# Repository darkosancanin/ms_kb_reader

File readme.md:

## Overview 
ATmega328 based Microsoft wireless keyboard reader with LCD display. 
The device passively scans for wireless keyboards in the vicinity of the device, then displays the characters typed on the LCD display. 
Based on code from KeySweeper (http://samy.pl/keysweeper/) by Samy Kamkar. 

## Keyboard Reader

## Schematic

## Breadboard

## PCB Layout

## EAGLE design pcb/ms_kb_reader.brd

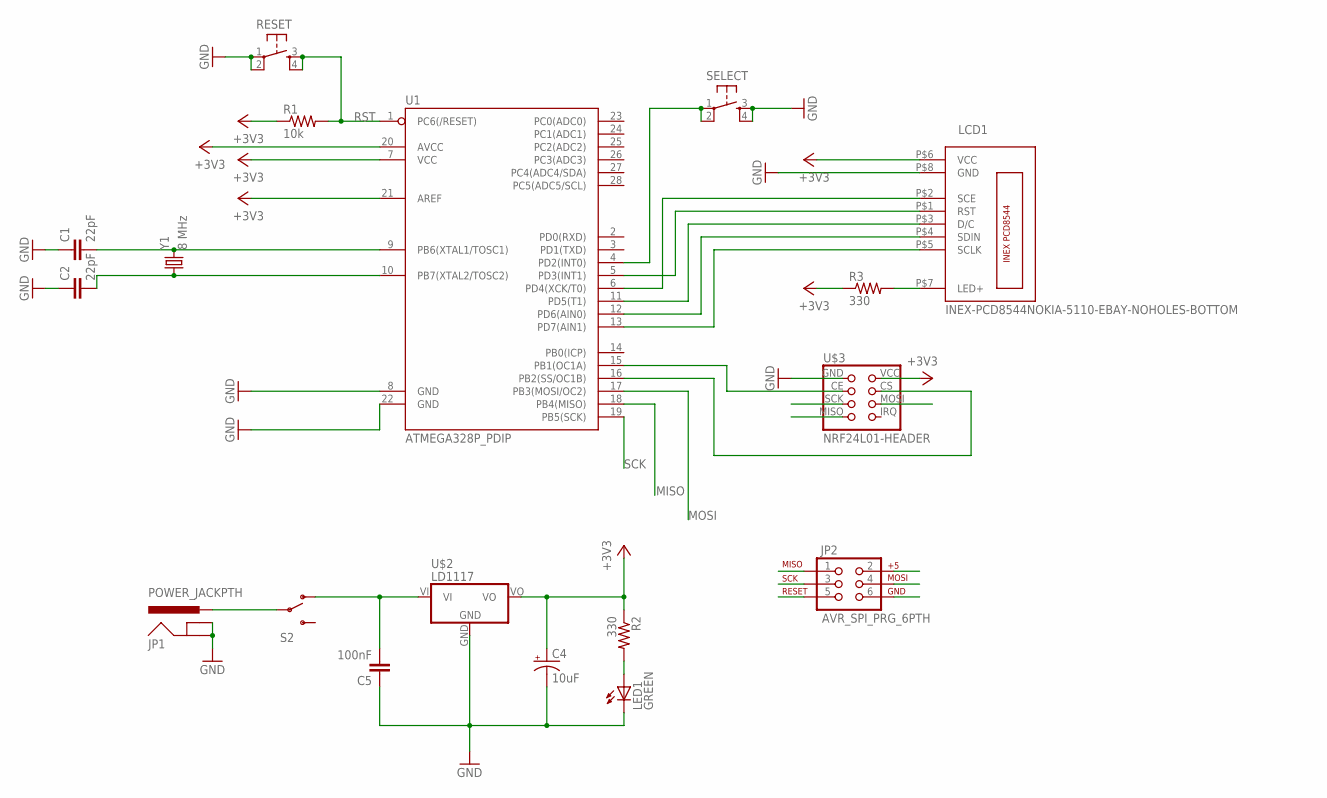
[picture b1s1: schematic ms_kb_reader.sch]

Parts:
C1, C2: 22pF; CAP-PTH-SMALL
C4: 10uF; E2,5-5
C5: 100nF; CAP-PTH-SMALL
JP1: POWER_JACKPTH; POWER_JACK_PTH
JP2: AVR_SPI_PRG_6PTH; 2X3
LCD1: INEX-PCD8544NOKIA-5110-EBAY-NOHOLES-BOTTOM; NOKIA-5110-EBAY-NOHOLES
LED1: GREEN; LED5MM
R1: 10k; 0207/10
R2, R3: 330; 0207/10
RESET: TACTILE-SWITCH-PTH; TAC-SWITCH-PTH
S2: SWITCH-SPDTPTH_LOCK; SWITCH-SPDT_LOCK.007S
SELECT: TACTILE-SWITCH-PTH; TAC-SWITCH-PTH
U1: ATMEGA328P_PDIP; DIL28-3
U$2: LD1117
U$3: NRF24L01-HEADER
Y1: 8 MHz; HC49US

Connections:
+3V3: C4.+, JP2.2, LCD1.P$6 (VCC), R1.1, R2.1, R3.1, U1.7 (VCC), U1.20 (AVCC), U1.21 (AREF), U$2.VO, U$3.VCC
GND: C1.1, C2.1, C4.-, C5.1, JP1.GND, JP1.GNDBREAK, JP2.6, LCD1.P$8 (GND), LED1.K (C), RESET.1, RESET.2, SELECT.3, SELECT.4, U1.8 (GND), U1.22 (GND), U$2.GND, U$3.GND
MISO: JP2.1, U1.18 (PB4(MISO)), U$3.MISO
MOSI: JP2.4, U1.17 (PB3(MOSI/OC2)), U$3.MOSI
unnamed: LCD1.P$1 (RST), U1.5 (PD3(INT1))
unnamed: LCD1.P$2 (SCE), U1.6 (PD4(XCK/T0))
unnamed: LCD1.P$3 (D/C), U1.11 (PD5(T1))
unnamed: LED1.A, R2.2
unnamed: C5.2, S2.1 (O), U$2.VI
unnamed: JP1.PWR, S2.2
unnamed: LCD1.P$4 (SDIN), U1.12 (PD6(AIN0))
unnamed: SELECT.1, SELECT.2, U1.4 (PD2(INT0))
unnamed: LCD1.P$5 (SCLK), U1.13 (PD7(AIN1))
unnamed: U1.16 (PB2(SS/OC1B)), U$3.CS
unnamed: C2.2, U1.10 (PB7(XTAL2/TOSC2)), Y1.1
unnamed: C1.2, U1.9 (PB6(XTAL1/TOSC1)), Y1.2
unnamed: U1.15 (PB1(OC1A)), U$3.CE
unnamed: LCD1.P$7 (LED+), R3.2
RST: JP2.5, R1.2, RESET.3, RESET.4, U1.1 (PC6(/RESET))
SCK: JP2.3, U1.19 (PB5(SCK)), U$3.SCK

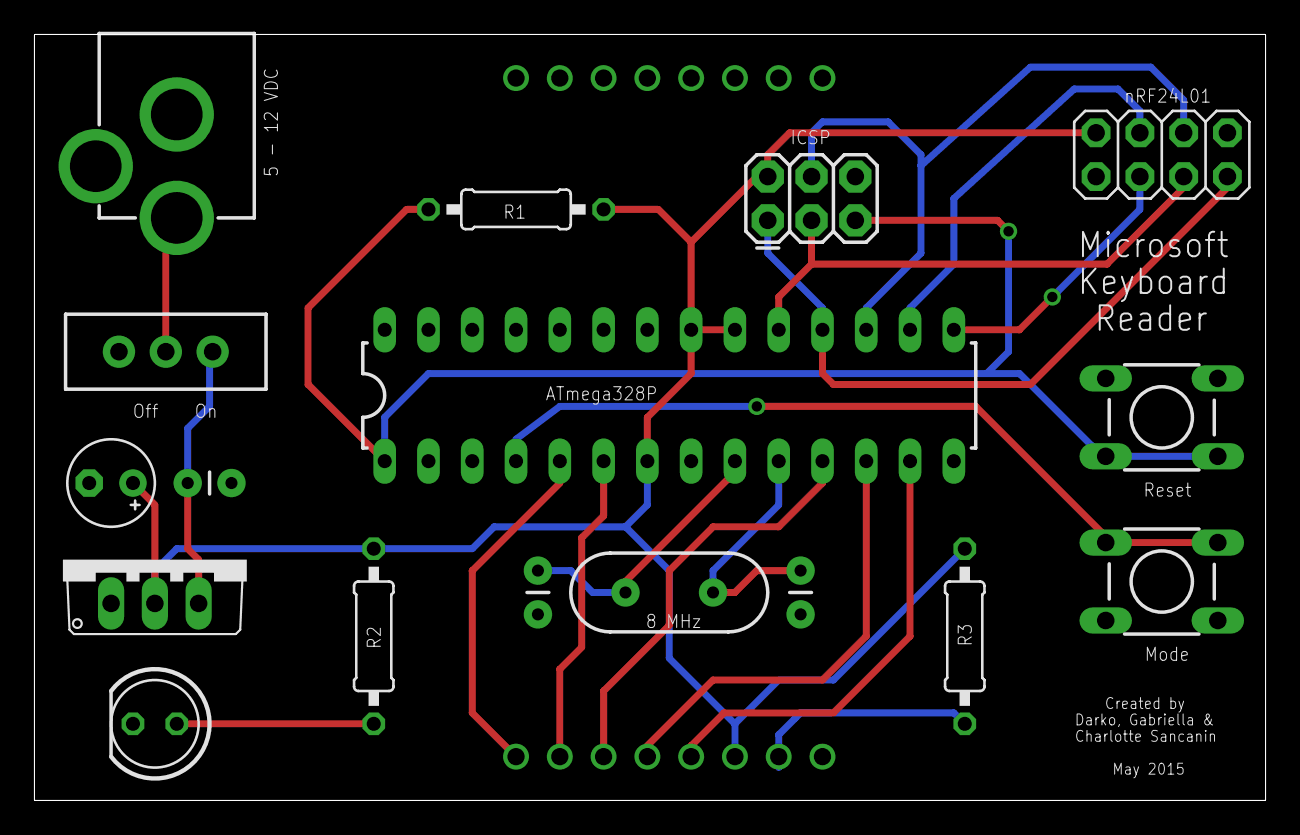
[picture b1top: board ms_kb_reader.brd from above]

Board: 2 copper layers, 71.4 x 44.4 mm, 18 parts (0 on the bottom side), 20 nets.

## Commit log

2015-04-18 Initial commit.
2015-04-19 Updated code and added sample output.
2015-04-19 Updated sample output to use text darkkko to see what repeat keys do.
2015-04-20 Updated code. Cleaned up some character recognition but still some bugs to sort out.
2015-04-20 Fixed minor bugs.
2015-04-23 Updated to incorporate LCD display.
2015-04-24 Cleaned up code and fixed some bugs.
2015-05-10 Added datasheets and updated code.
2015-05-10 Fixed minor display bugs and commented out SD card.
2015-05-10 Removed SD card code from project.
2015-05-10 Fixed buffer bug.
2015-05-10 Fixed bug with status screen getting overwritten.
2015-05-10 Added deboucing to mode button.
2015-05-13 Looping through common channels a few times during scan now.
2015-05-13 Added relevant libraries.
2015-05-13 Fixed bug with loop through common channels.
2015-05-13 Changed contrast to work with second LCD screen.
2015-05-14 Updated pins for LCD.
2015-05-14 Added eagle libraries.
2015-05-14 Added PCB drawings.
2015-05-17 Added eagle files, pcb images and updated readme.
2015-06-11 Updated readme.
2015-07-30 Added images of finished product to readme.

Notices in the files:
parts and their libraries:
SparkFun-Capacitors: Licensing: Creative Commons ShareAlike 4.0 International - https://creativecommons.org/licenses/by-sa/4.0
